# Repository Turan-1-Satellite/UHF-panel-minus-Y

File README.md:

# Turan-1 UHF Panel −Y in KiCad

## About

This repository contains the KiCad 9.0 project files for the **TURAN-1 UHF Panel −Y PCB** — a directional UHF-band antenna panel mounted on the (−Y) face of the Turan-1 CubeSat, providing UHF communications coverage (400–450 MHz) in the boresight direction of that panel.

---

## Requirements

- KiCad 9.0 or later

---

## First Set Up

All required custom libraries and 3D models are included as a git submodule. To clone the repository together with custom libraries, you need to recursively clone it:

```bash
git clone --recurse-submodules https://github.com/Turan-1-Satellite/UHF-panel-minus-Y.git
```

---

## Open the Project

Open the `UHF-panel-minus-Y.kicad_pro` file from the project root directory.

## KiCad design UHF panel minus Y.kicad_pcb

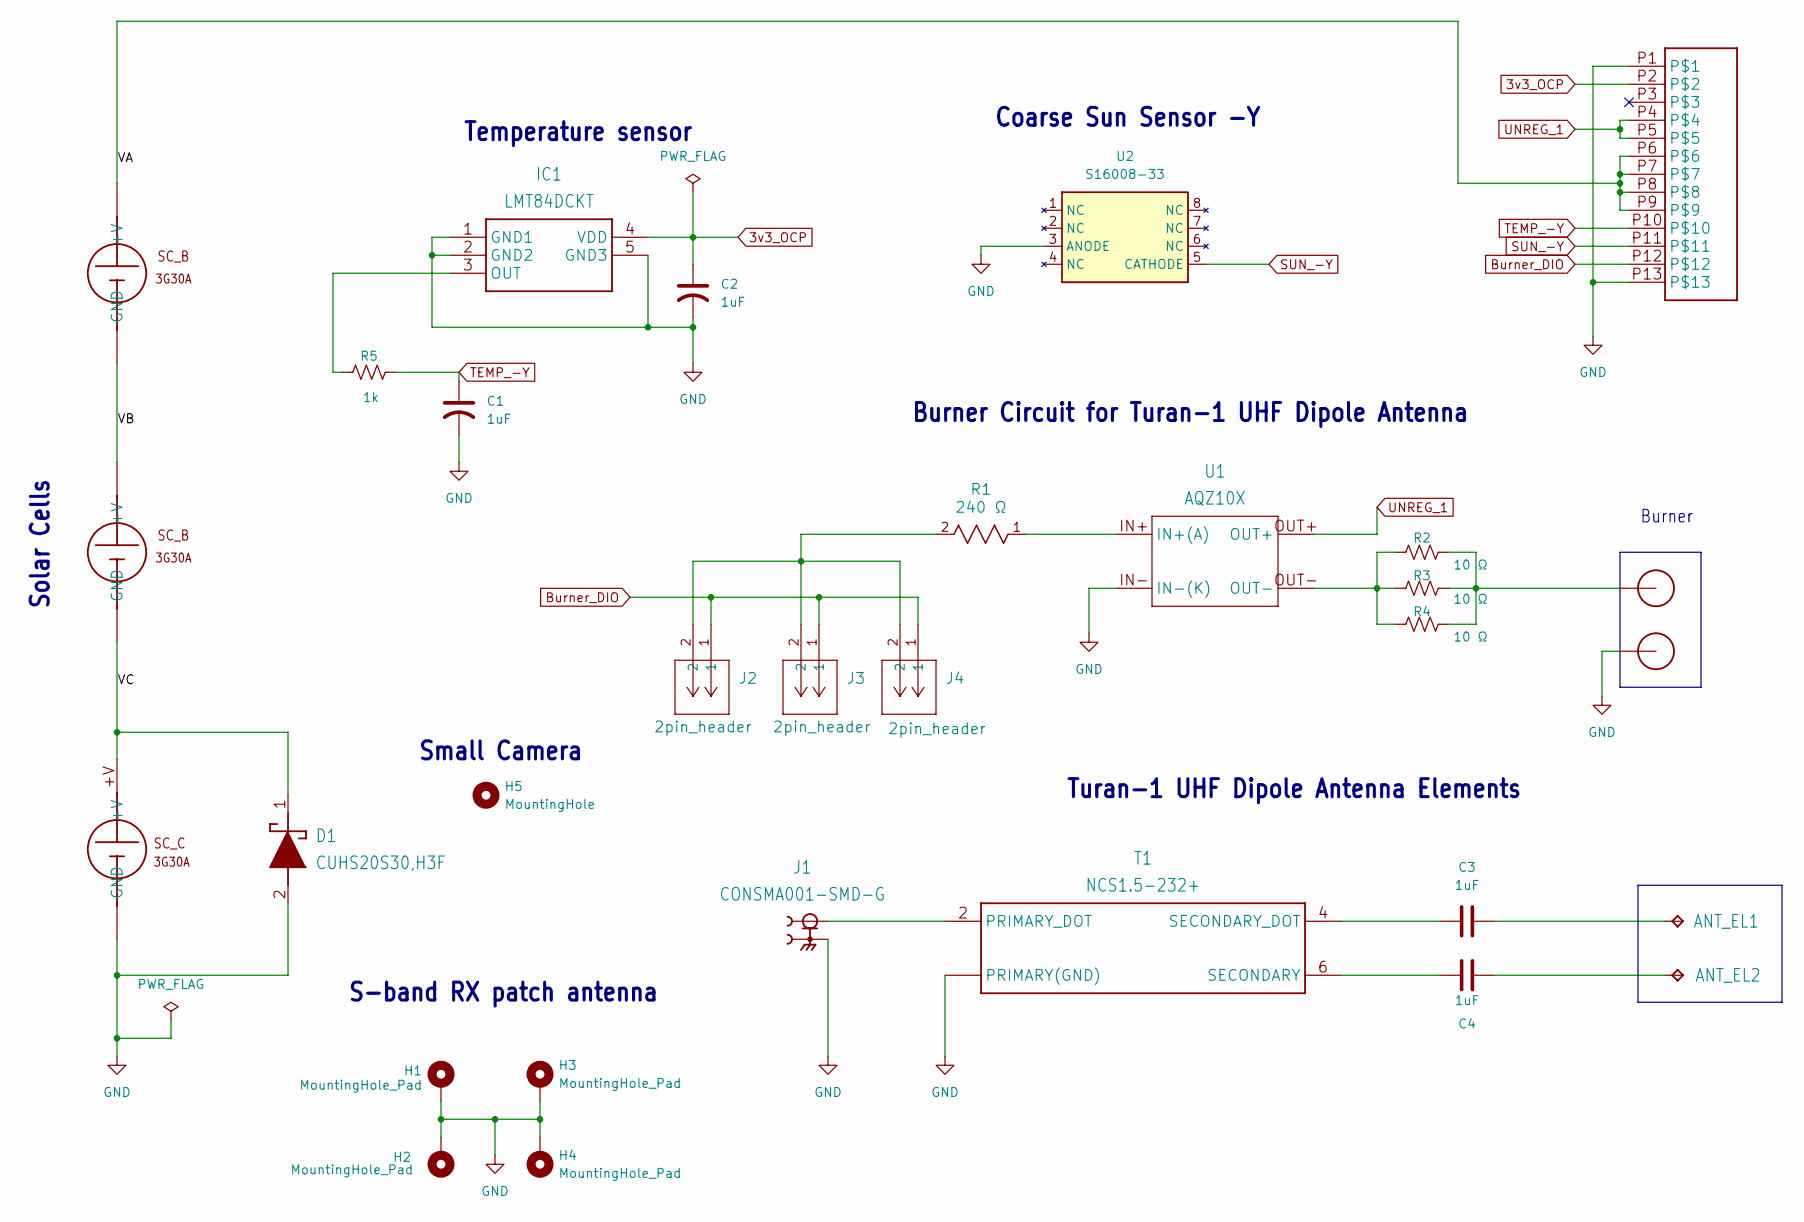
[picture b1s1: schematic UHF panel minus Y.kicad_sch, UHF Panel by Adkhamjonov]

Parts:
ANT_EL1: ANT_EL_1
ANT_EL2: ANT_EL_2
C1, C2: 1uF; C_0805_2012Metric
C3, C4: 1uF; C_0603_1608Metric
D1: CUHS20S30,H3F
H1, H2, H3, H4: MountingHole_Pad; MountingHole_2 mm_M2_Custom_Pad_TopOnly
H5: MountingHole; MountingHole_2.1mm
IC1: LMT84DCKT
J1: CONSMA001-SMD-G; SMA connector
J2, J3, J4: 2pin_header; 2pin header
R1: 240 Ω; RESC1005X35N
R2, R3, R4: 10 Ω; R_AXIAL_SMD
R5: 1k; R_0805_2012Metric
S1: Solar_cell_C; solar_cell_C
S2, S3: solar_cell_B
T1: NCS1.5-232+; LTTC Transformer
U1: AQZ10X; PHOTOMOS_AQZ10X
U2: S16008-33
U$1: 13pin_connector
U$2, U$3: NICR_HOLE; NICR_Hole

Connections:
3v3_OCP: C2.1, IC1.4 (VDD), U$1.P2
/VA: S3.+V, U$1.P6, U$1.P7, U$1.P8, U$1.P9
/VB: S2.+V, S3.GND
/VC: D1.1 (K), S1.+V, S2.GND
Burner_DIO: J2.1, J3.1, J4.1, U$1.P12
GND: C1.2, C2.2, D1.2 (A), H1.1, H2.1, H3.1, H4.1, IC1.1 (GND1), IC1.2 (GND2), IC1.5 (GND3), J1.S1 (2), J1.S2 (2), S1.GND, T1.1 (PRIMARY(GND)), T1.3 (PRIMARY(GND)), U1.IN- (IN-(K)), U2.3 (ANODE), U$1.P1, U$1.P13, U$3.P$1
unnamed: ANT_EL1.TP, C3.2
unnamed: ANT_EL2.TP, C4.2
unnamed: IC1.3 (OUT), R5.1
unnamed: J2.2, J3.2, J4.2, R1.2
unnamed: R2.1, R3.1, R4.1, U1.OUT-
unnamed: R2.2, R3.2, R4.2, U$2.P$1
unnamed: J1.1, T1.2 (PRIMARY_DOT)
unnamed: C4.1, T1.6 (SECONDARY)
unnamed: C3.1, T1.4 (SECONDARY_DOT)
unnamed: R1.1, U1.IN+ (IN+(A))
SUN_-Y: U2.5 (CATHODE), U$1.P11
TEMP_-Y: C1.1, R5.2, U$1.P10
UNREG_1: U1.OUT+, U$1.P4, U$1.P5

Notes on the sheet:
Burner
Small Camera
Burner Circuit for Turan-1 UHF Dipole Antenna
Solar Cells
Temperature sensor
Turan-1 UHF Dipole Antenna Elements
Coarse Sun Sensor -Y
S-band RX patch antenna

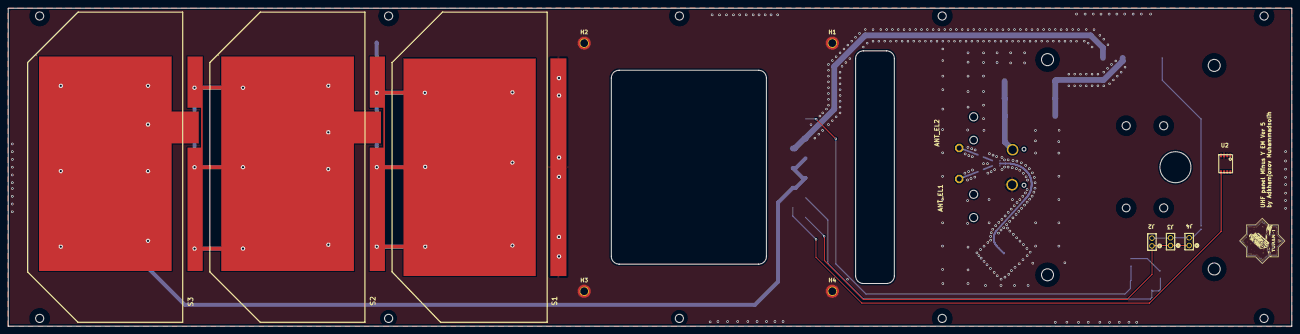
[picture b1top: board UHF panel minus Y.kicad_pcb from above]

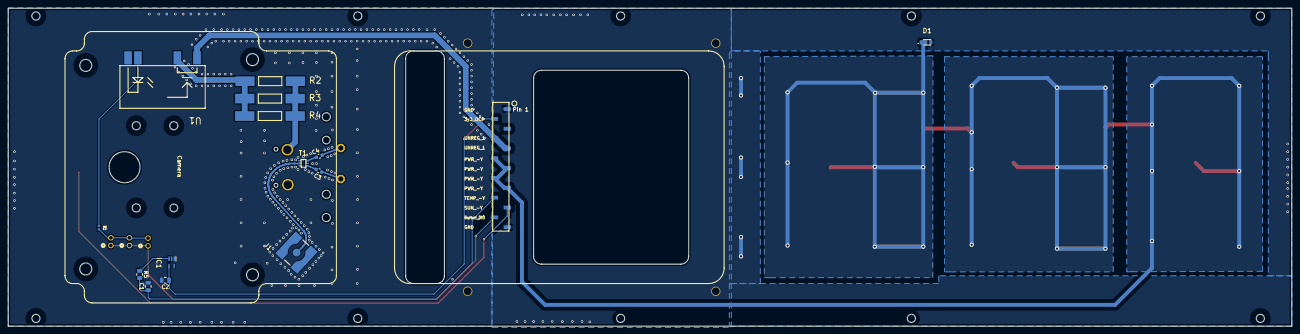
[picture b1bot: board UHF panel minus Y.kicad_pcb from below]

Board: 4 copper layers, 331.0 x 82.0 mm, 31 parts (15 on the bottom side), 19 nets.

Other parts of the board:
Camera: MountingHole; MountingHole_2.1mm

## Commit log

2026-04-07 Initial commit for UHF panel -Y
2026-04-07 Fix solar cell connections
2026-04-10 Update the library
2026-04-10 change the fill zone size
2026-04-12 Added logo and name for the panel
2026-04-12 Change the small camera position
2026-04-12 Add README for Turan-1 UHF Panel -Y
2026-04-13 Added small camera
2026-04-15 Add 3D for burner resistors
2026-04-25 Change the grounding of solar panel power lines
